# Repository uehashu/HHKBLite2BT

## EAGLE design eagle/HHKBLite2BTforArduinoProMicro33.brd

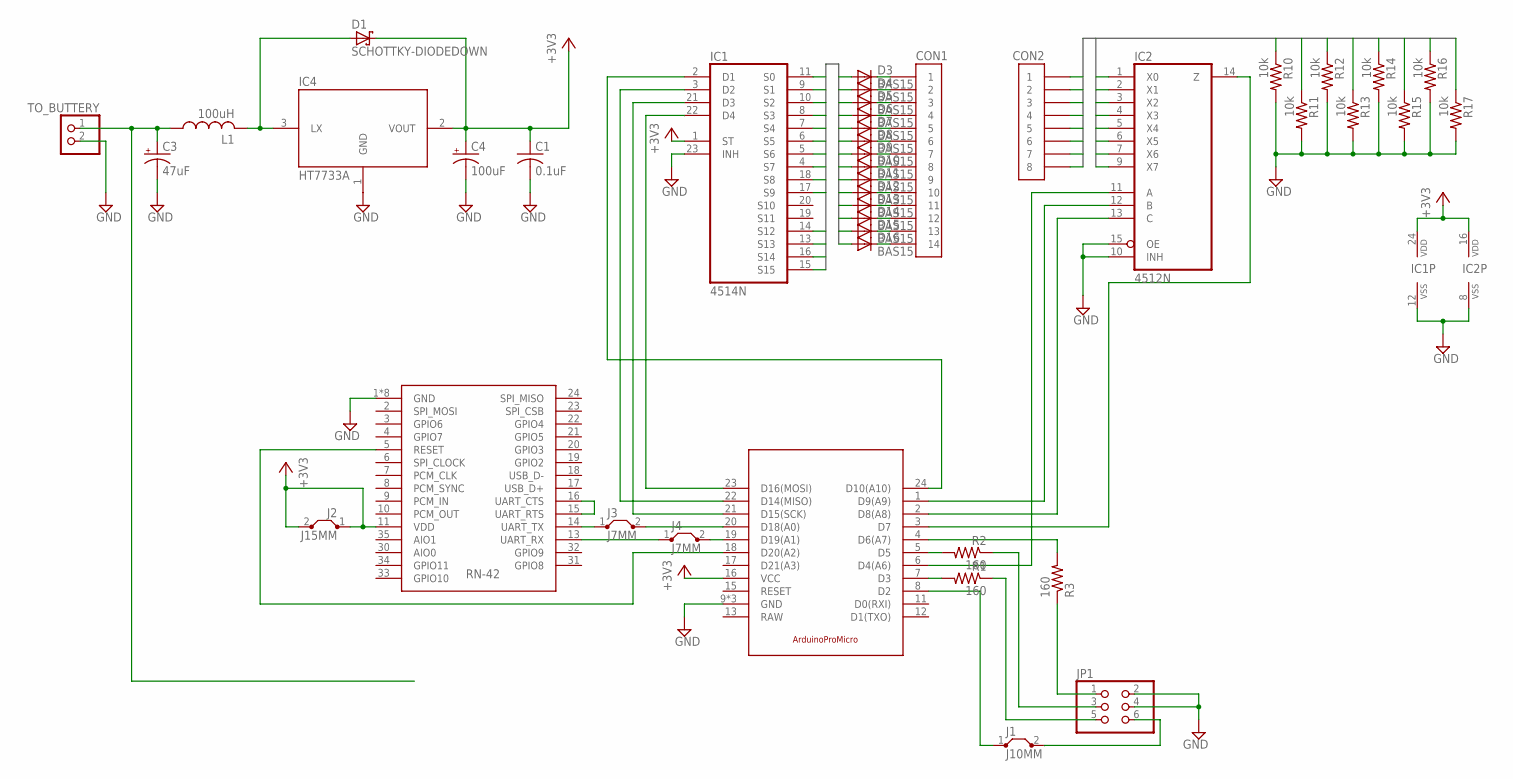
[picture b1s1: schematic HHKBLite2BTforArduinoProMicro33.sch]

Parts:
C1: 0.1uF; C050-024X044
C3: 47uF; E2,5-7
C4: 100uF; E2,5-7
CON1: 45045-1445; 52045-1445
CON2: 45045-0845; 52045-0845
D1: SCHOTTKY-DIODEDOWN; DIODE-STAND-DOWN
D3, D4, D5, D6, D7, D8, D9, D10, D11, D12, D13, D14, D15, D16: BAS15; DO34-7
IC1: 4514N; DIL24-6
IC2: 4512N; DIL16
IC4: HT7733A; TO-92
J1: J10MM; 10
J2: J15MM; 15
J3, J4: J7MM; 07
JP1: PINHD-2X3/90; 2X03/90
L1: 100uH; E5-10
R1, R2: 160; 0207/7
R3: 160; 0207/10
R10, R11, R12, R14, R15, R16, R17: 10k; 0207/7
R13: 10k; 0207/10
TO_BUTTERY: PINHD-1X2; 1X02
U$1: RN-42
U$2: ARDUINO_PRO_MICRO

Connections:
+3V3: C1.1, C4.+, D1.C, IC1.1 (ST), IC1.24 (VDD), IC2.16 (VDD), IC4.2 (VOUT), J2.1, J2.2, U$1.11 (VDD), U$2.16 (VCC)
CON1BUS_O0: D3.A, IC1.11 (S0)
CON1BUS_O1: D5.A, IC1.9 (S1)
CON1BUS_O2: D4.A, IC1.10 (S2)
CON1BUS_O3: D6.A, IC1.8 (S3)
CON1BUS_O4: D7.A, IC1.7 (S4)
CON1BUS_O5: D8.A, IC1.6 (S5)
CON1BUS_O6: D9.A, IC1.5 (S6)
CON1BUS_O7: D10.A, IC1.4 (S7)
CON1BUS_O8: D11.A, IC1.18 (S8)
CON1BUS_O9: D16.A, IC1.17 (S9)
CON1BUS_O12: D13.A, IC1.14 (S12)
CON1BUS_O13: D12.A, IC1.13 (S13)
CON1BUS_O14: D15.A, IC1.16 (S14)
CON1BUS_O15: D14.A, IC1.15 (S15)
CON2BUS_D0: CON2.8, IC2.1 (X0), R10.1
CON2BUS_D1: CON2.7, IC2.2 (X1), R11.1
CON2BUS_D2: CON2.6, IC2.3 (X2), R12.1
CON2BUS_D3: CON2.5, IC2.4 (X3), R13.1
CON2BUS_D4: CON2.4, IC2.5 (X4), R14.1
CON2BUS_D5: CON2.3, IC2.6 (X5), R15.1
CON2BUS_D6: CON2.2, IC2.7 (X6), R16.1
CON2BUS_D7: CON2.1, IC2.9 (X7), R17.1
GND: C1.2, C3.-, C4.-, IC1.12 (VSS), IC1.23 (INH), IC2.8 (VSS), IC2.10 (INH), IC2.15 (OE), IC4.1 (GND), JP1.2, JP1.4, R10.2, R11.2, R12.2, R13.2, R14.2, R15.2, R16.2, R17.2, TO_BUTTERY.2, U$1.1 (GND), U$1.12 (GND), U$1.28 (GND), U$1.29 (GND), U$1.GND1 (GND), U$1.GND2 (GND), U$1.GND3 (GND), U$1.GND4 (GND), U$2.9 (GND), U$2.10 (GND), U$2.14 (GND)
unnamed: R3.2, U$2.4 (D6(A7))
unnamed: R1.2, U$2.7 (D3)
unnamed: D1.A, IC4.3 (LX), L1.+1 (2)
unnamed: R2.2, U$2.5 (D5)
unnamed: J3.1, U$1.14 (UART_TX)
unnamed: U$1.5 (RESET), U$2.18 (D20(A2))
unnamed: J3.2, U$2.20 (D18(A0))
unnamed: JP1.1, R3.1
unnamed: IC2.14 (Z), U$2.3 (D7)
unnamed: JP1.3, R2.1
unnamed: JP1.5, R1.1
unnamed: J1.2, JP1.6
unnamed: J1.1, U$2.8 (D2)
unnamed: J4.1, U$1.13 (UART_RX)
unnamed: IC2.12 (B), U$2.1 (D9(A9))
unnamed: IC2.13 (C), U$2.2 (D8(A8))
unnamed: J4.2, U$2.19 (D19(A1))
unnamed: U$1.15 (UART_RTS), U$1.16 (UART_CTS)
unnamed: IC2.11 (A), U$2.6 (D4(A6))
unnamed: IC1.2 (D1), U$2.24 (D10(A10))
unnamed: IC1.3 (D2), U$2.22 (D14(MISO))
unnamed: IC1.21 (D3), U$2.21 (D15(SCK))
unnamed: IC1.22 (D4), U$2.23 (D16(MOSI))
unnamed: CON1.1, D3.C
unnamed: CON1.2, D4.C
unnamed: CON1.3, D5.C
unnamed: CON1.4, D6.C
unnamed: CON1.5, D7.C
unnamed: CON1.6, D8.C
unnamed: CON1.7, D9.C
unnamed: CON1.8, D10.C
unnamed: CON1.9, D11.C
unnamed: CON1.10, D12.C
unnamed: CON1.11, D13.C
unnamed: CON1.12, D14.C
unnamed: CON1.13, D15.C
unnamed: CON1.14, D16.C
VCC_SRC: C3.+, L1.+ (1), TO_BUTTERY.1

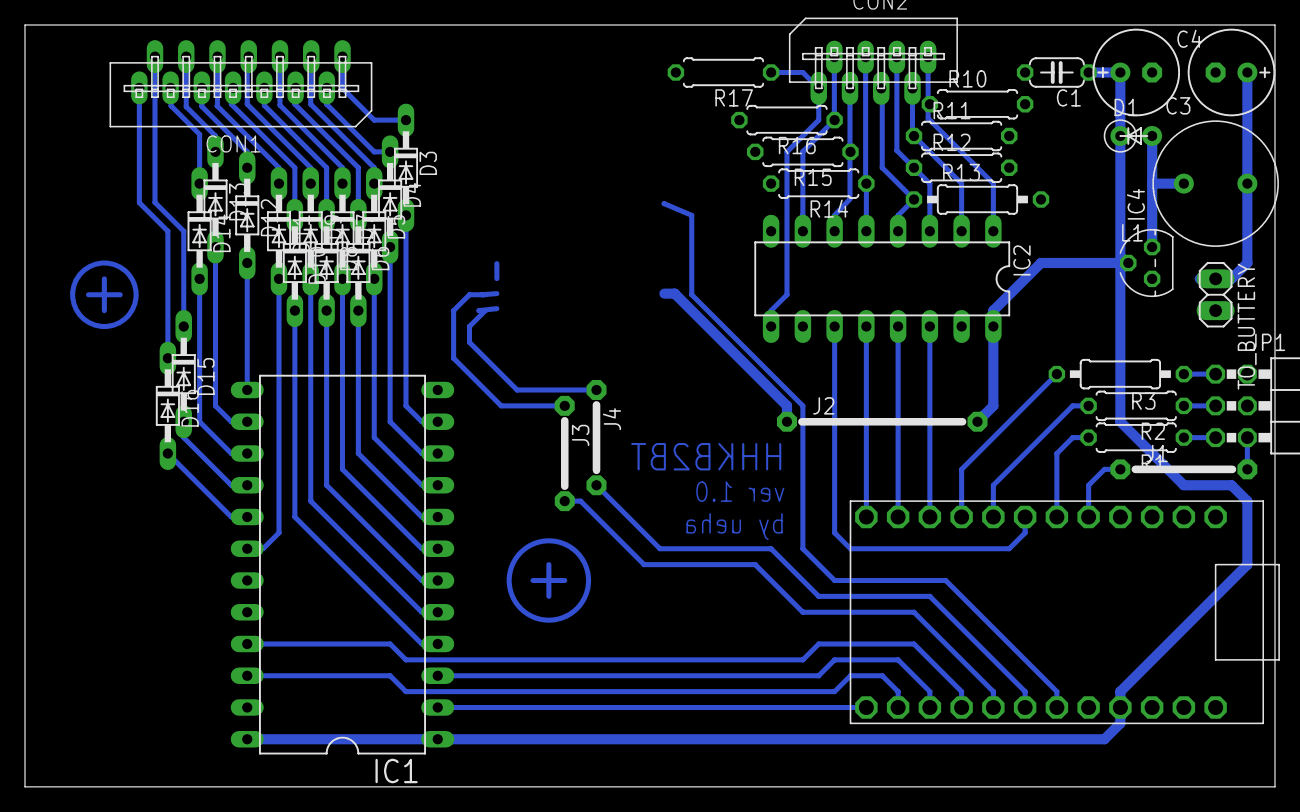
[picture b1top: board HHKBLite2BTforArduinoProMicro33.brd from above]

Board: 2 copper layers, 100.0 x 61.0 mm, 43 parts (1 on the bottom side), 62 nets.

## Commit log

2014-04-09 Initial commit.
2014-05-04 基板を作成。
    これまでは Arduino のpin1からpinNまでを順番につないでいたが、
    基板に起こしやすいよう、接続の順番を基板用に書き換えた。
    加えて、基板を作成した。
2014-08-20 Arduino Pro Micro33 を用いた回路図を追加.
2014-08-24 いろいろ変えた
    回路図については, 電源周りとかアライメントとかを調節した.
    また, パーツのサイズを, 実際に使いそうなサイズにフィットさせた.
    プログラムは移動させた.
2014-09-02 ProMicro33用コードと回路図を変更
    各ICとのピンの番号が整合するように調節した.
2014-09-03 コメントとかを修正
    三単現のs付いてなかったし, sweep を sweap と typo してた...
2014-09-08 入力ピンをINPUTからINPUT_PULLUPに変更
    内部プルアップ抵抗を使うように書き換えた.
    それに伴い, 該当箇所の真理値を逆転させた.
2014-09-08 フローチャートの追加と, 適切なアルゴリズムへの変更
    ちゃんと動作させるために, フローチャートを作成した.
    そのアルゴリズムに則り, スケッチを変更してある.
    ピン番号や基板はまだ修正していないので注意してほしいよ.
2015-04-22 Arduino IDE 1.6.x のためにいろいろ変更.
    Arduino IDE 1.6.x と Arduino-Makefile でこのプロジェクトをコンパイルできるように
    するために, いろいろいじった.
    まだ試験的なものなので, 今回変更した Makefile を参考にし, 他のものも
    書き換えると良い.
    あと, ProMicro33 に関して言えば, これをそのまま使ってもコンパイルできない.
    SparkFun から適切なボードコンフィグを持ってきて, 適切な場所に置き,
2016-02-11 Arduino IDE v1.6.7 および SparkFun Arduino Library v1.1.3 に対応
    知らぬ間にいろいろバージョンが上がってたみたいで, Arduino.mk とソースコードが
    動かなくなっていた.
    動くように適切に修正したっぽ.
    Arduino.mk は OS X に特化させたので, Linux では動かなくなっているはず.
2016-02-11 Uno 用のテストコードも Arduino IDE 1.6.7 に追従.
